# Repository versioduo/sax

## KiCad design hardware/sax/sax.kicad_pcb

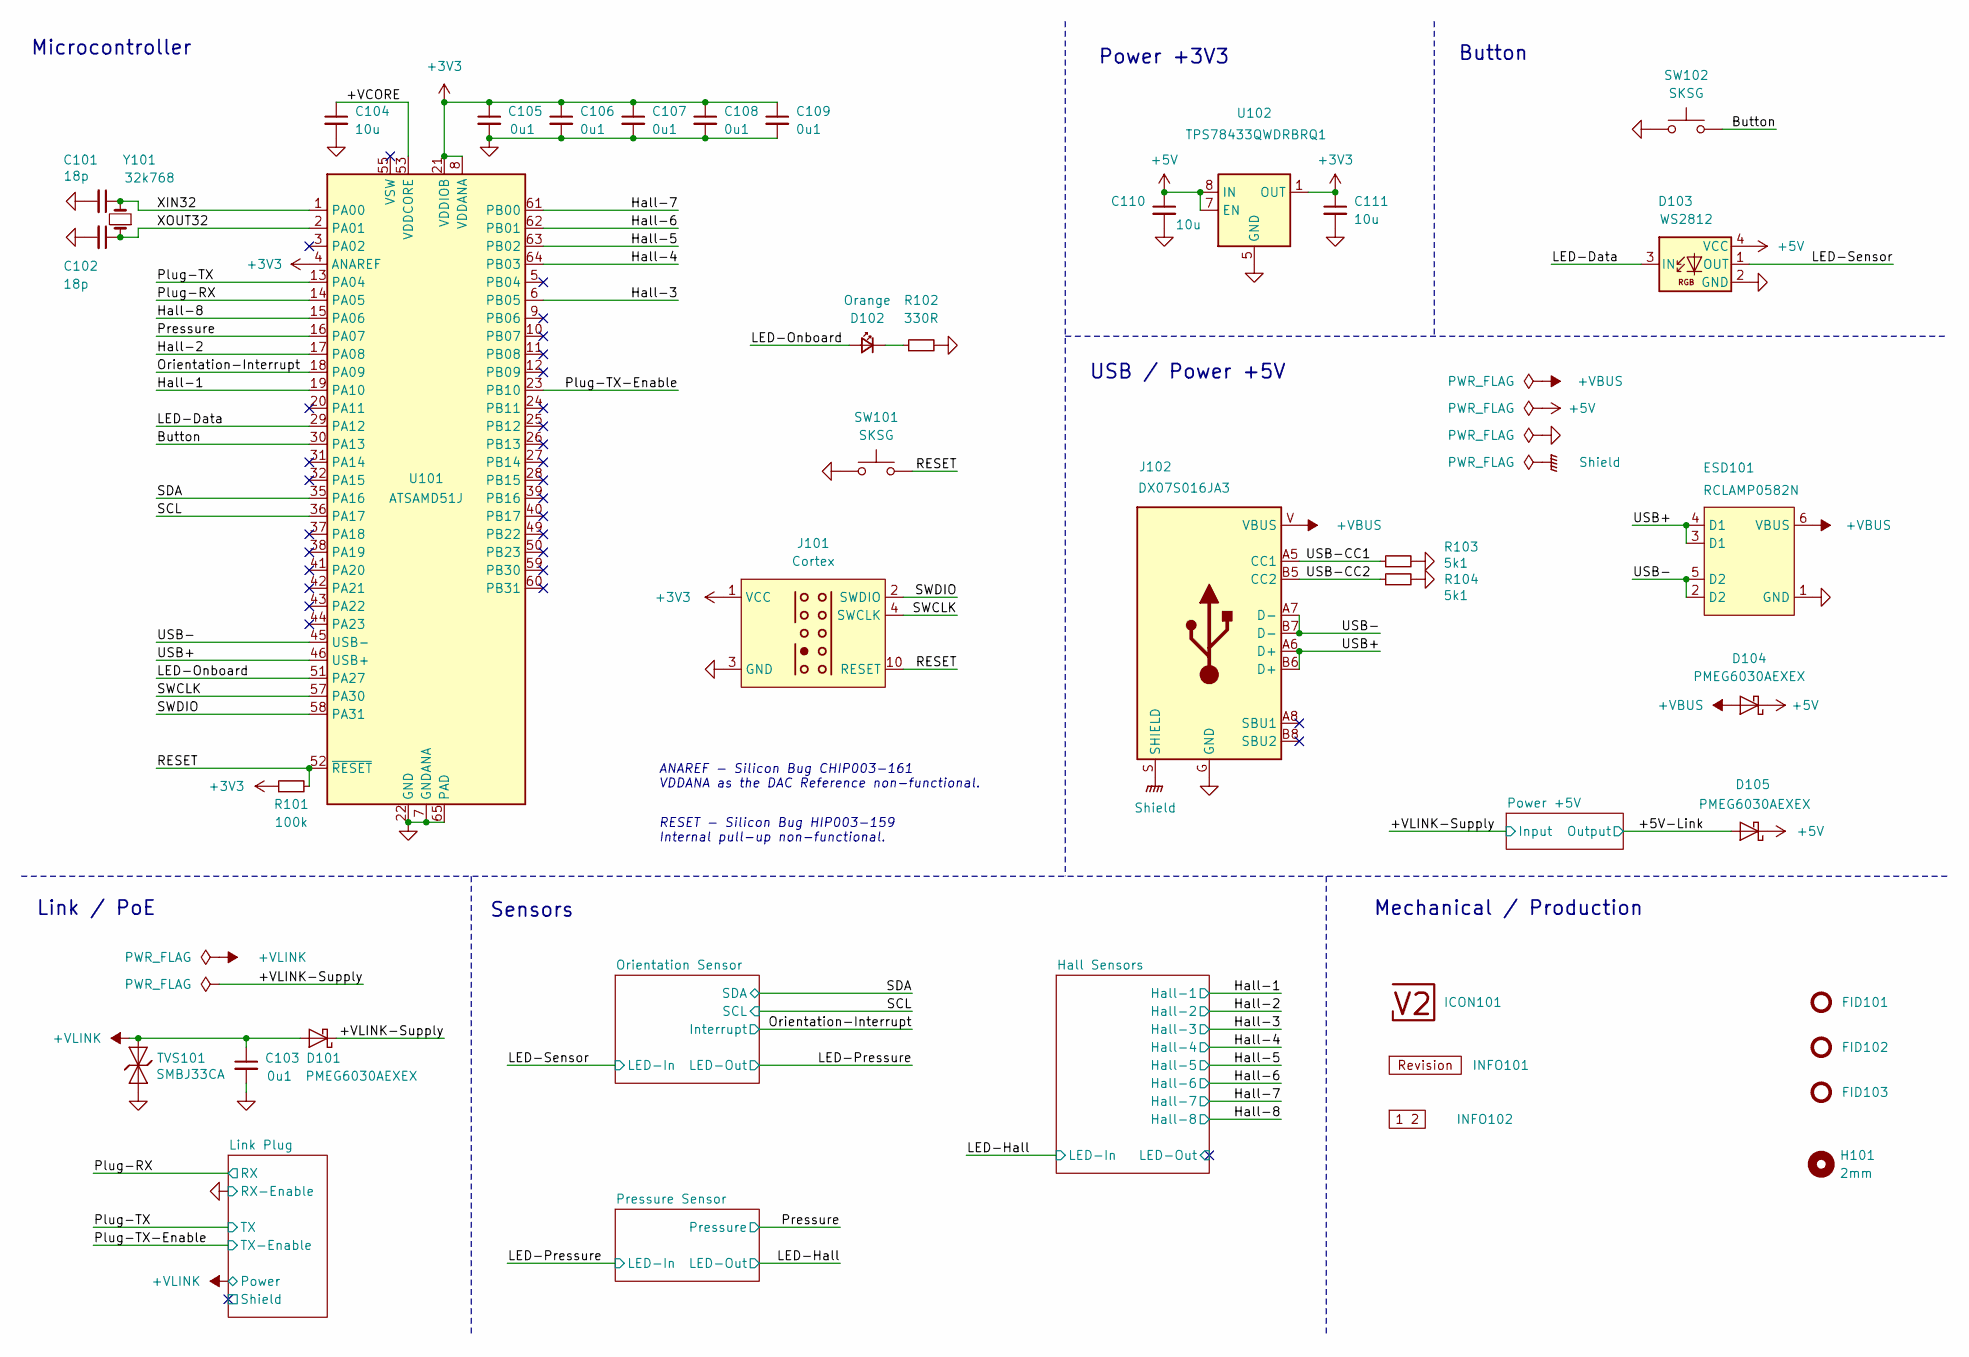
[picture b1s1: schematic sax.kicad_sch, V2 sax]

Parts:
C101, C102: 18p; C_1608; Rating 50V; Mouser 810-CGA3E2C0G1H180J
C103, C105, C106, C107, C108, C109: 0u1; C_1608; Rating 50V; Mouser 810-CGA3E2X7R1H104MA
C104: 10u; C_1608; Rating 10V; Mouser 810-C1608X6S1A106M
C110, C111: 10u; C_2012; Rating 25V; Mouser 810-C2012X5R1E106K
D101, D104, D105: PMEG6030AEXEX; D_SOD-123HP; Rating 60V; Mouser 771-PMEG6030AEXEX
D102: Orange; LED_1608; Rating 605nm; Mouser 755-SML-D12D1WT86
D103: WS2812; WS2812-2020; Rating 15mA; LCSC C965555
ESD101: RCLAMP0582N; SLP1210N6; Rating 20kV; Mouser 947-RCLAMP0582N.TCT
FID101, FID102, FID103: Fiducial_Paste; Fiducial_0.5mm_Mask1mm_Paste
H101: 2mm; MountingHole_2mm
ICON101: V2-logo; Logo_Small
INFO101: Revision
INFO102: Layer_Numbers-4
J101: Cortex
J102: DX07S016JA3; JAE_DX07S016JA3; Rating USB2.0; Mouser 656-DX07S016JA3R1500
R101: 100k; R_1608; Rating 100mW; Mouser 71-CRCW0603100KFKEAC
R102: 330R; R_1608; Rating 100mW; Mouser 71-CRCW0603330RFKEAC
R103, R104: 5k1; R_1608; Rating 100mW; Mouser 71-CRCW06035K10FKEAC
SW101, SW102: SKSG; Rating 1.6N; Mouser 688-SKSGACE010
TVS101: SMBJ33CA; D_SMB; Rating 33V; Mouser 652-SMBJ33CA-Q
U101: ATSAMD51J; QFN-64-1EP_9x9mm_P0.5mm_EP4.8x4.8mm_ThermalVias; Rating Cortex-M4F; Mouser 556-ATSAMD51J19AMU
U102: TPS78433QWDRBRQ1; VSON-8-1_3x3mm_P0.65_EP1.65x2.4mm; Rating 300mA; Mouser 595-TPS78433QWDRBRQ1
Y101: 32k768; Crystal_SMD_3215-2Pin_3.2x1.5mm; Rating 10ppm; Mouser 815-ABS0716632.768KT

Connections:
+3V3: C105.1, C106.1, C107.1, C108.1, C109.1, C111.1, J101.1 (VCC), R101.1, U101.4 (ANAREF), U101.8 (VDDANA), U101.21 (VDDIOB), U101.34 (VDDIO), U101.48 (VDDIO), U101.56 (VDDIO), U102.1 (OUT); also elsewhere on the board
+5V: C110.1, D103.4 (VCC), D104.1 (K), D105.1 (K), U102.7 (EN), U102.8 (IN); also elsewhere on the board
/+5V-Link: D105.2 (A); also elsewhere on the board
/+VBUS: D104.2 (A), ESD101.6 (VBUS), J102.V (VBUS)
/+VCORE: C104.1, U101.53 (VDDCORE)
/+VLINK: C103.1, D101.2 (A), TVS101.2 (A); also elsewhere on the board
/+VLINK-Supply: D101.1 (K); also elsewhere on the board
/Button: SW102.2, U101.30 (PA13)
/Hall-1: U101.19 (PA10); also elsewhere on the board
/Hall-2: U101.17 (PA08); also elsewhere on the board
/Hall-3: U101.6 (PB05); also elsewhere on the board
/Hall-4: U101.64 (PB03); also elsewhere on the board
/Hall-5: U101.63 (PB02); also elsewhere on the board
/Hall-6: U101.62 (PB01); also elsewhere on the board
/Hall-7: U101.61 (PB00); also elsewhere on the board
/Hall-8: U101.15 (PA06); also elsewhere on the board
/LED-Data: D103.3 (IN), U101.29 (PA12)
/LED-Onboard: D102.2 (A), U101.51 (PA27)
/LED-Sensor: D103.1 (OUT); also elsewhere on the board
/Orientation-Interrupt: U101.18 (PA09); also elsewhere on the board
/Plug-RX: U101.14 (PA05); also elsewhere on the board
/Plug-TX: U101.13 (PA04); also elsewhere on the board
/Plug-TX-Enable: U101.23 (PB10); also elsewhere on the board
/Pressure: U101.16 (PA07); also elsewhere on the board
/RESET: J101.10 (RESET), R101.2, SW101.2, U101.52 (~RESET)
/SCL: U101.36 (PA17); also elsewhere on the board
/SDA: U101.35 (PA16); also elsewhere on the board
/SWCLK: J101.4 (SWCLK), U101.57 (PA30)
/SWDIO: J101.2 (SWDIO), U101.58 (PA31)
/Shield: J102.S (SHIELD)
/USB+: ESD101.3 (D1), ESD101.4 (D1), J102.A6 (D+), J102.B6 (D+), U101.46 (USB+)
/USB-: ESD101.2 (D2), ESD101.5 (D2), J102.A7 (D-), J102.B7 (D-), U101.45 (USB-)
/USB-CC1: J102.A5 (CC1), R103.1
/USB-CC2: J102.B5 (CC2), R104.1
/XIN32: C101.1, U101.1 (PA00), Y101.2
/XOUT32: C102.1, U101.2 (PA01), Y101.1
GND: C101.2, C102.2, C103.2, C104.2, C105.2, C106.2, C107.2, C108.2, C109.2, C110.2, C111.2, D103.2 (GND), ESD101.1 (GND), J101.3 (GND), J101.5 (GND), J102.G (GND), R102.2, R103.2, R104.2, SW101.1, SW102.1, TVS101.1 (K), U101.7 (GNDANA), U101.22 (GND), U101.33 (GND), U101.47 (GND), U101.54 (GND), U101.65 (PAD), U102.5 (GND), U102.9 (GND); also elsewhere on the board
unnamed: D102.1 (K), R102.1

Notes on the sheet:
ANAREF - Silicon Bug CHIP003-161 VDDANA as the DAC Reference non-functional.
Sensors
Link / PoE
RESET - Silicon Bug HIP003-159 Internal pull-up non-functional.
Button
Power +3V3
Mechanical / Production
Microcontroller
USB / Power +5V

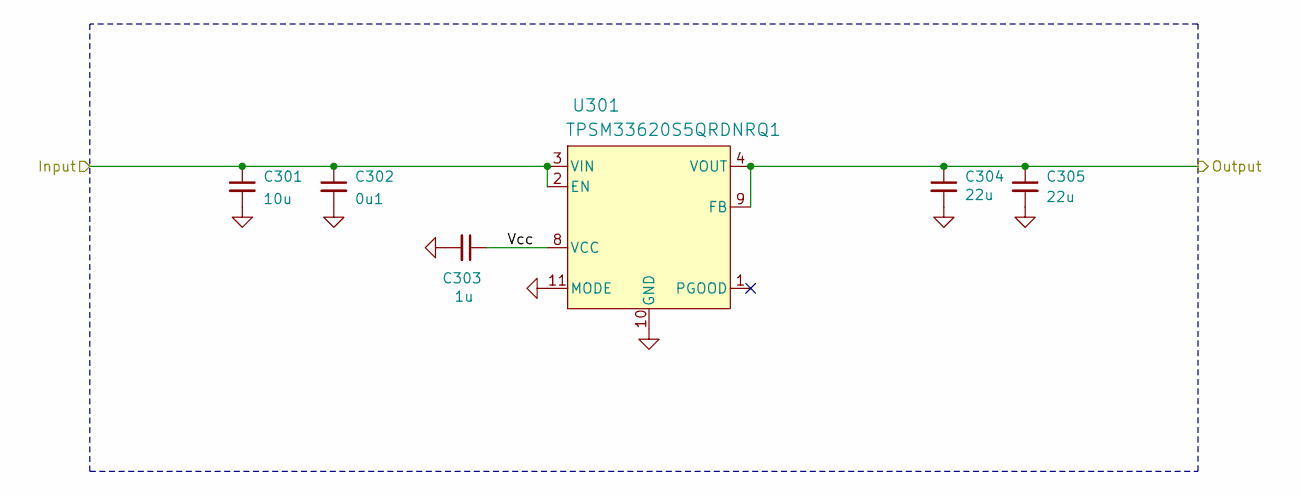
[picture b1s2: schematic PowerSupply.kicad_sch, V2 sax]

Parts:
C301: 10u; C_3225; Rating 50V; Mouser 810-CNC6P1X7R1H106K2
C302: 0u1; C_1608; Rating 50V; Mouser 810-CGA3E2X7R1H104MA
C303: 1u; C_1608; Rating 50V; Mouser 810-CGA3E3X7R1H105K0
C304, C305: 22u; C_3225; Rating 25V; Mouser 810-CGA6P3X7R1E226M5
U301: TPSM33620S5QRDNRQ1; QFN-11; Rating 2A; Mouser 595-SM33620S5QRDNRQ1

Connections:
/+5V-Link: C304.1, C305.1, U301.4 (VOUT), U301.9 (FB); also elsewhere on the board
/+VLINK-Supply: C301.1, C302.1, U301.2 (EN), U301.3 (VIN); also elsewhere on the board
/Power +5V/Vcc: C303.1, U301.8 (VCC)
GND: C301.2, C302.2, C303.2, C304.2, C305.2, U301.10 (GND), U301.11 (MODE); also elsewhere on the board

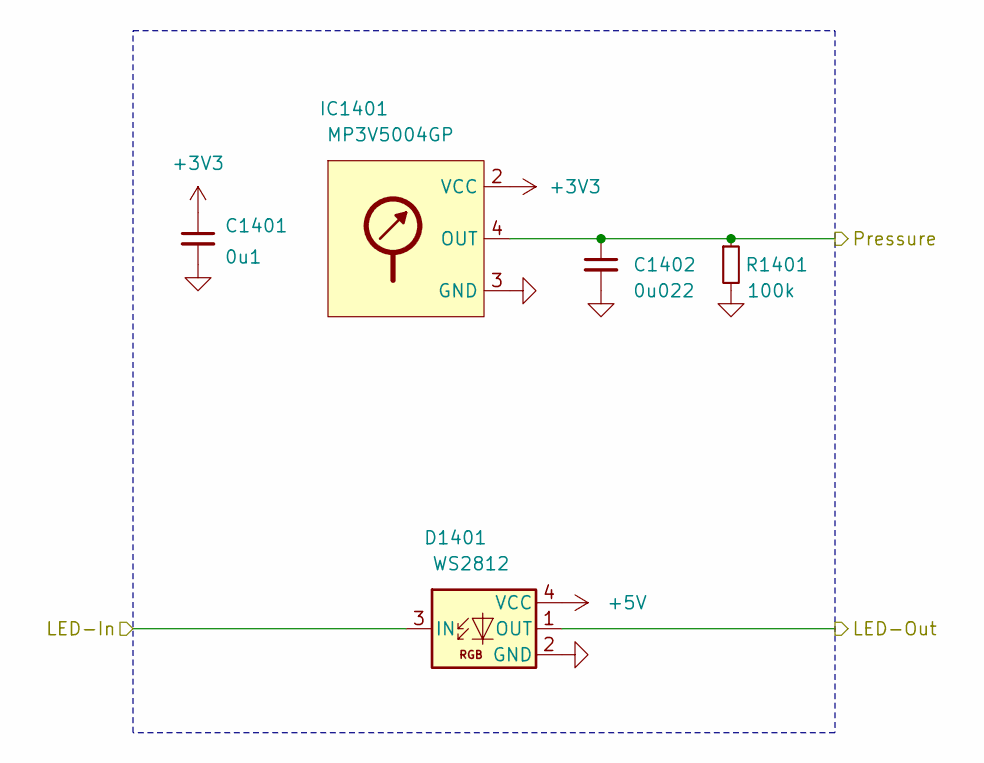
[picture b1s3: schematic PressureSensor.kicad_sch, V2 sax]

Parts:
C1401: 0u1; C_1608; Rating 50V; Mouser 810-CGA3E2X7R1H104MA
C1402: 0u022; C_1608; Rating 50V; Mouser 603-CC603KPX7R9BB223
D1401: WS2812; WS2812-2020; Rating 15mA; LCSC C965555
IC1401: MP3V5004GP; Rating 3.92 kPa; Mouser 841-MP3V5004GP
R1401: 100k; R_1608; Rating 100mW; Mouser 71-CRCW0603100KFKEAC

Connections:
+3V3: C1401.1, IC1401.2 (VCC); also elsewhere on the board
+5V: D1401.4 (VCC); also elsewhere on the board
/LED-Hall: D1401.1 (OUT); also elsewhere on the board
/LED-Pressure: D1401.3 (IN); also elsewhere on the board
/Pressure: C1402.1, IC1401.4 (OUT), R1401.1; also elsewhere on the board
GND: C1401.2, C1402.2, D1401.2 (GND), IC1401.3 (GND), R1401.2; also elsewhere on the board

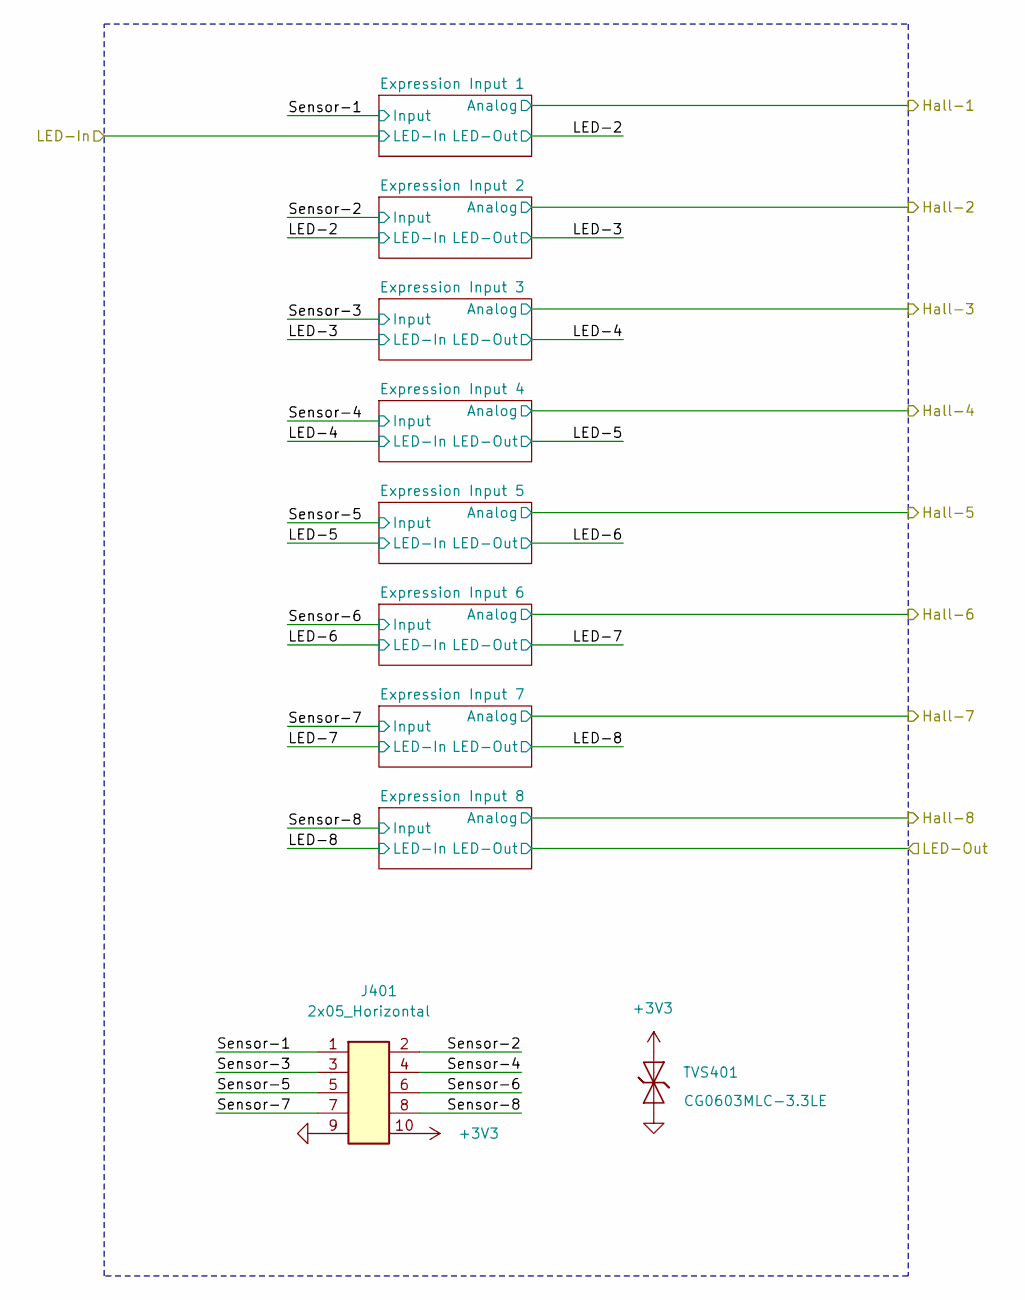
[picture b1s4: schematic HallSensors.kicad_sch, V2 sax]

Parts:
J401: 2x05_Horizontal; PinHeader_2x05_P1.27mm_Horizontal; Rating 1A; Mouser 649-200211120001T4LF
TVS401: CG0603MLC-3.3LE; D_1608; Rating 3V3; Mouser 652-CG0603MLC-3.3LE

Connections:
+3V3: J401.10, TVS401.1 (K); also elsewhere on the board
/Hall Sensors/Sensor-1: J401.1; also elsewhere on the board
/Hall Sensors/Sensor-2: J401.2; also elsewhere on the board
/Hall Sensors/Sensor-3: J401.3; also elsewhere on the board
/Hall Sensors/Sensor-4: J401.4; also elsewhere on the board
/Hall Sensors/Sensor-5: J401.5; also elsewhere on the board
/Hall Sensors/Sensor-6: J401.6; also elsewhere on the board
/Hall Sensors/Sensor-7: J401.7; also elsewhere on the board
/Hall Sensors/Sensor-8: J401.8; also elsewhere on the board
GND: J401.9, TVS401.2 (A); also elsewhere on the board

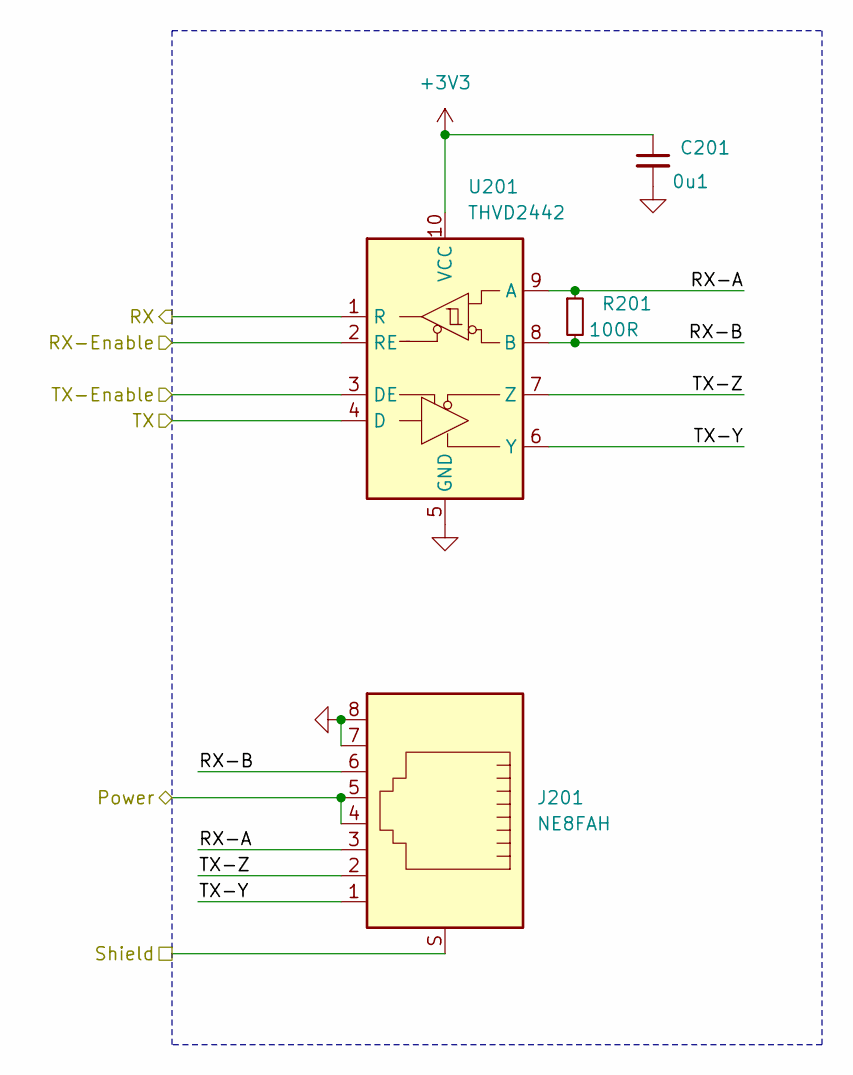
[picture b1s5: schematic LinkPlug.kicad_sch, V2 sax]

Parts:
C201: 0u1; C_1608; Rating 50V; Mouser 810-CGA3E2X7R1H104MA
J201: NE8FAH; Rating CAT5e; Mouser 568-NE8FAH
R201: 100R; R_1608; Rating 330mW; Mouser 71-CRCW0603100RFKEAH
U201: THVD2442; VSON-10-4-1EP_3x3mm_P0.5mm_EP1.65x2.4mm_ThermalVias; Rating 20Mbps; Mouser 595-THVD2442DRCR

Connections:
+3V3: C201.1, U201.10 (VCC); also elsewhere on the board
/+VLINK: J201.4, J201.5; also elsewhere on the board
/Link Plug/RX-A: J201.3, R201.1, U201.9 (A)
/Link Plug/RX-B: J201.6, R201.2, U201.8 (B)
/Link Plug/Shield: J201.S
/Link Plug/TX-Y: J201.1, U201.6 (Y)
/Link Plug/TX-Z: J201.2, U201.7 (Z)
/Plug-RX: U201.1 (R); also elsewhere on the board
/Plug-TX: U201.4 (D); also elsewhere on the board
/Plug-TX-Enable: U201.3 (DE); also elsewhere on the board
GND: C201.2, J201.7, J201.8, U201.2 (RE), U201.5 (GND), U201.11 (GND); also elsewhere on the board

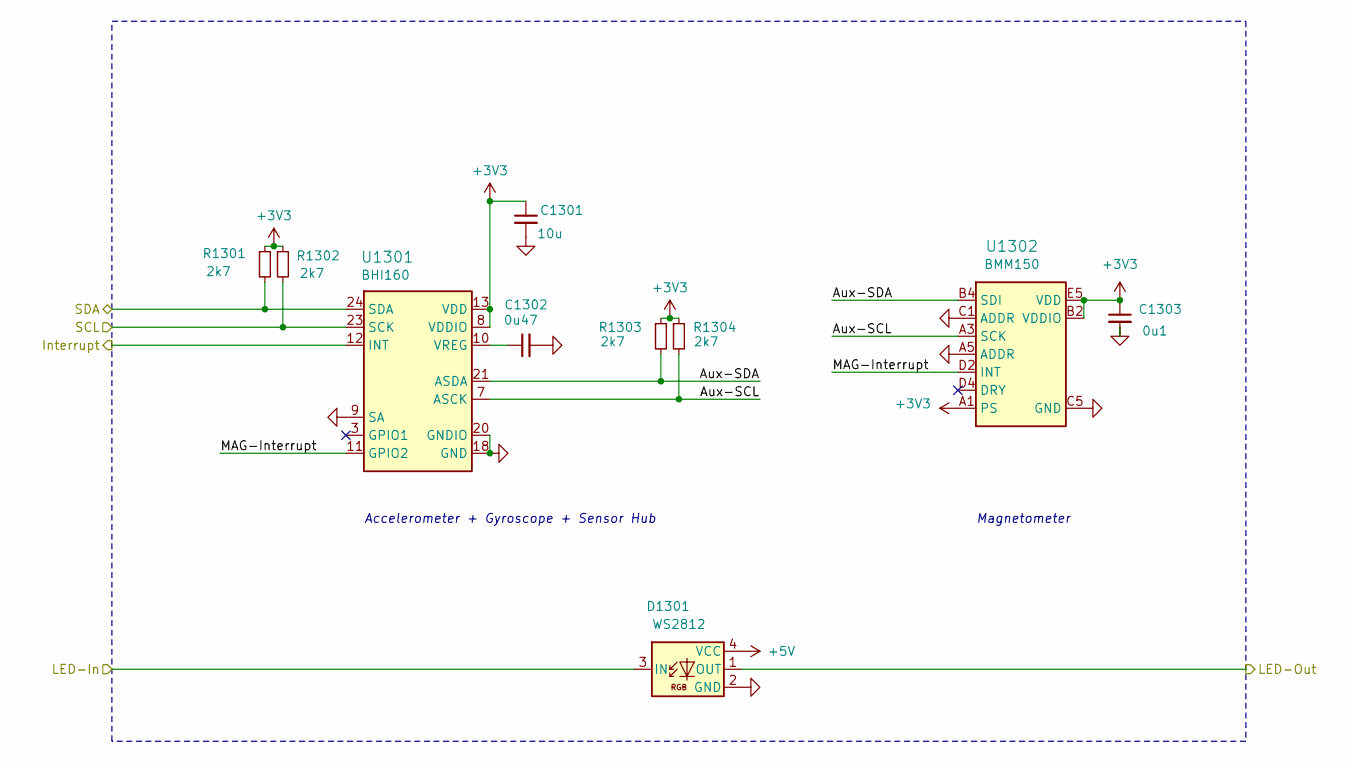
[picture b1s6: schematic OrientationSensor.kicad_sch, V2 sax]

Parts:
C1301: 10u; C_1608; Rating 10V; Mouser 810-C1608X6S1A106M
C1302: 0u47; C_1608; Rating 50V; Mouser 810-CGA3E3X7R1H474KB
C1303: 0u1; C_1608; Rating 50V; Mouser 810-CGA3E2X7R1H104MA
D1301: WS2812; WS2812-2020; Rating 15mA; LCSC C965555
R1301, R1302, R1303, R1304: 2k7; R_1608; Rating 100mW; Mouser 71-CRCW06032K70FKEAC
U1301: BHI160; LGA24-3x3; LCSC C464452
U1302: BMM150; WLCSP-1.56x1.56; LCSC C171681

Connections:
+3V3: C1301.1, C1303.1, R1301.1, R1302.1, R1303.1, R1304.1, U1301.8 (VDDIO), U1301.13 (VDD), U1302.A1 (PS), U1302.B2 (VDDIO), U1302.E5 (VDD); also elsewhere on the board
+5V: D1301.4 (VCC); also elsewhere on the board
/LED-Pressure: D1301.1 (OUT); also elsewhere on the board
/LED-Sensor: D1301.3 (IN); also elsewhere on the board
/Orientation Sensor/Aux-SCL: R1304.2, U1301.7 (ASCK), U1302.A3 (SCK)
/Orientation Sensor/Aux-SDA: R1303.2, U1301.21 (ASDA), U1302.B4 (SDI)
/Orientation Sensor/MAG-Interrupt: U1301.11 (GPIO2), U1302.D2 (INT)
/Orientation-Interrupt: U1301.12 (INT); also elsewhere on the board
/SCL: R1302.2, U1301.23 (SCK); also elsewhere on the board
/SDA: R1301.2, U1301.24 (SDA); also elsewhere on the board
GND: C1301.2, C1302.2, C1303.2, D1301.2 (GND), U1301.9 (SA), U1301.18 (GND), U1301.20 (GNDIO), U1302.A5 (ADDR), U1302.C1 (ADDR), U1302.C5 (GND), U1302.E1 (GND), U1302.E3 (GND); also elsewhere on the board
unnamed: C1302.1, U1301.10 (VREG)

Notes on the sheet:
Accelerometer + Gyroscope + Sensor Hub
Magnetometer

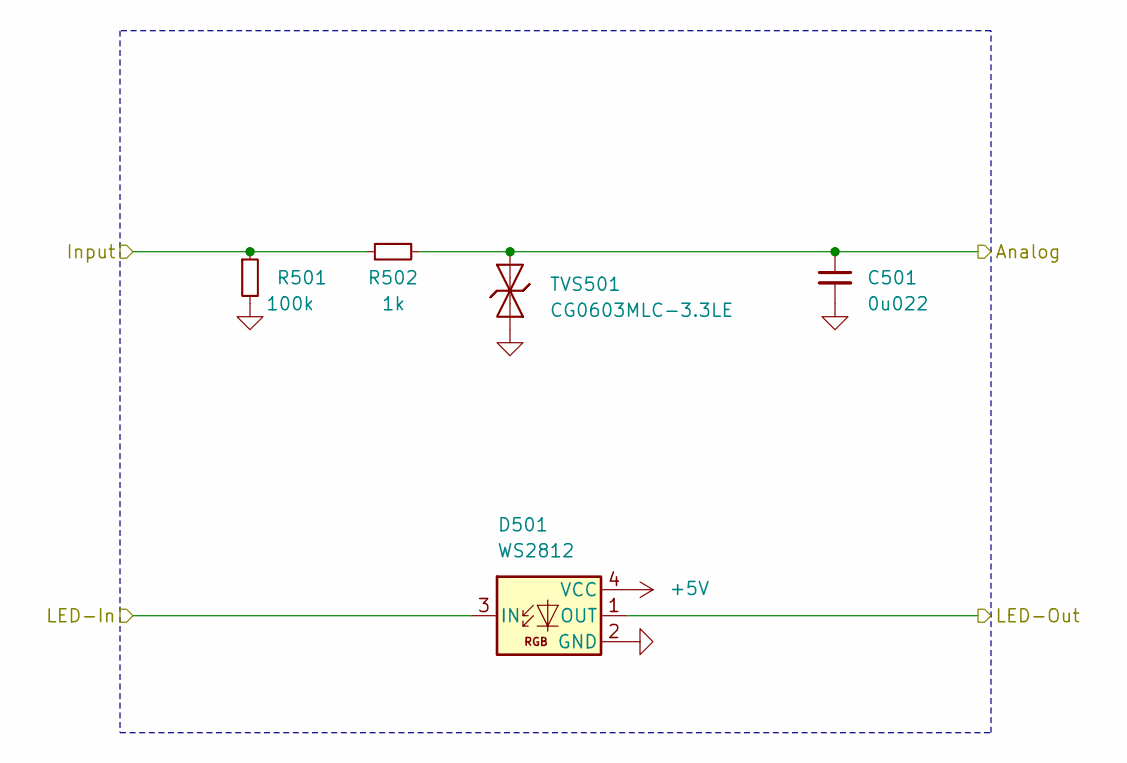
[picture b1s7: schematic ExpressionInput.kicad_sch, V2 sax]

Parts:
C501: 0u022; C_1608; Rating 50V; Mouser 603-CC603KPX7R9BB223
D501: WS2812; WS2812-2020; Rating 15mA; LCSC C965555
R501: 100k; R_1608; Rating 100mW; Mouser 71-CRCW0603100KFKEAC
R502: 1k; R_1608; Rating 330mW; Mouser 71-CRCW06031K00FKEAH
TVS501: CG0603MLC-3.3LE; D_1608; Rating 3V3; Mouser 652-CG0603MLC-3.3LE

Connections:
+5V: D501.4 (VCC); also elsewhere on the board
/Hall Sensors/LED-2: D501.1 (OUT); also elsewhere on the board
/Hall Sensors/Sensor-1: R501.1, R502.2; also elsewhere on the board
/Hall-1: C501.1, R502.1, TVS501.2 (A); also elsewhere on the board
/LED-Hall: D501.3 (IN); also elsewhere on the board
GND: C501.2, D501.2 (GND), R501.2, TVS501.1 (K); also elsewhere on the board

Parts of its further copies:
C601, C701, C801, C901, C1001, C1101, C1201: 0u022; C_1608; Rating 50V; Mouser 603-CC603KPX7R9BB223
D601, D701, D801, D901, D1001, D1101, D1201: WS2812; WS2812-2020; Rating 15mA; LCSC C965555
R601, R701, R801, R901, R1001, R1101, R1201: 100k; R_1608; Rating 100mW; Mouser 71-CRCW0603100KFKEAC
R602, R702, R802, R902, R1002, R1102, R1202: 1k; R_1608; Rating 330mW; Mouser 71-CRCW06031K00FKEAH
TVS601, TVS701, TVS801, TVS901, TVS1001, TVS1101, TVS1201: CG0603MLC-3.3LE; D_1608; Rating 3V3; Mouser 652-CG0603MLC-3.3LE

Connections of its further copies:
+5V: D601.4 (VCC), D701.4 (VCC), D801.4 (VCC), D901.4 (VCC), D1001.4 (VCC), D1101.4 (VCC), D1201.4 (VCC); also elsewhere on the board
/Hall Sensors/LED-2: D601.3 (IN); also elsewhere on the board
/Hall Sensors/LED-3: D601.1 (OUT), D701.3 (IN)
/Hall Sensors/LED-4: D701.1 (OUT), D801.3 (IN)
/Hall Sensors/LED-5: D801.1 (OUT), D901.3 (IN)
/Hall Sensors/LED-6: D901.1 (OUT), D1001.3 (IN)
/Hall Sensors/LED-7: D1001.1 (OUT), D1101.3 (IN)
/Hall Sensors/LED-8: D1101.1 (OUT), D1201.3 (IN)
/Hall Sensors/LED-Out: D1201.1 (OUT)
/Hall Sensors/Sensor-2: R601.1, R602.2; also elsewhere on the board
/Hall Sensors/Sensor-3: R701.1, R702.2; also elsewhere on the board
/Hall Sensors/Sensor-4: R801.1, R802.2; also elsewhere on the board
/Hall Sensors/Sensor-5: R901.1, R902.2; also elsewhere on the board
/Hall Sensors/Sensor-6: R1001.1, R1002.2; also elsewhere on the board
/Hall Sensors/Sensor-7: R1101.1, R1102.2; also elsewhere on the board
/Hall Sensors/Sensor-8: R1201.1, R1202.2; also elsewhere on the board
/Hall-2: C601.1, R602.1, TVS601.2 (A); also elsewhere on the board
/Hall-3: C701.1, R702.1, TVS701.2 (A); also elsewhere on the board
/Hall-4: C801.1, R802.1, TVS801.2 (A); also elsewhere on the board
/Hall-5: C901.1, R902.1, TVS901.2 (A); also elsewhere on the board
/Hall-6: C1001.1, R1002.1, TVS1001.2 (A); also elsewhere on the board
/Hall-7: C1101.1, R1102.1, TVS1101.2 (A); also elsewhere on the board
/Hall-8: C1201.1, R1202.1, TVS1201.2 (A); also elsewhere on the board
GND: C601.2, C701.2, C801.2, C901.2, C1001.2, C1101.2, C1201.2, D601.2 (GND), D701.2 (GND), D801.2 (GND), D901.2 (GND), D1001.2 (GND), D1101.2 (GND), D1201.2 (GND), R601.2, R701.2, R801.2, R901.2, R1001.2, R1101.2, R1201.2, TVS601.1 (K), TVS701.1 (K), TVS801.1 (K), TVS901.1 (K), TVS1001.1 (K), TVS1101.1 (K), TVS1201.1 (K); also elsewhere on the board

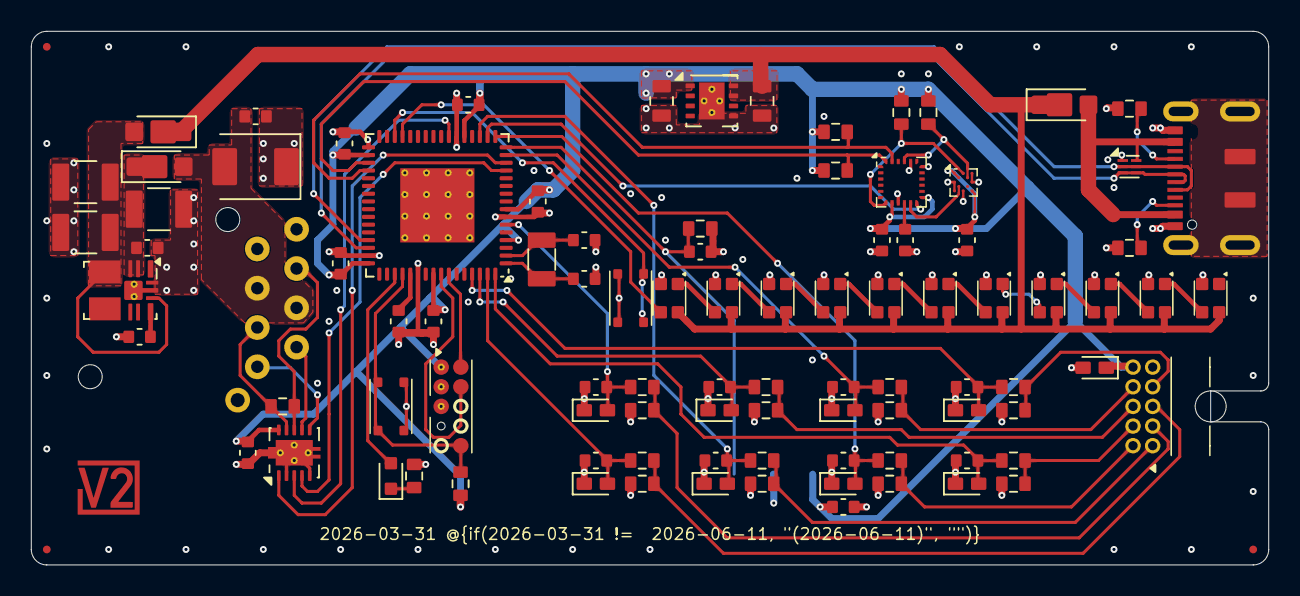
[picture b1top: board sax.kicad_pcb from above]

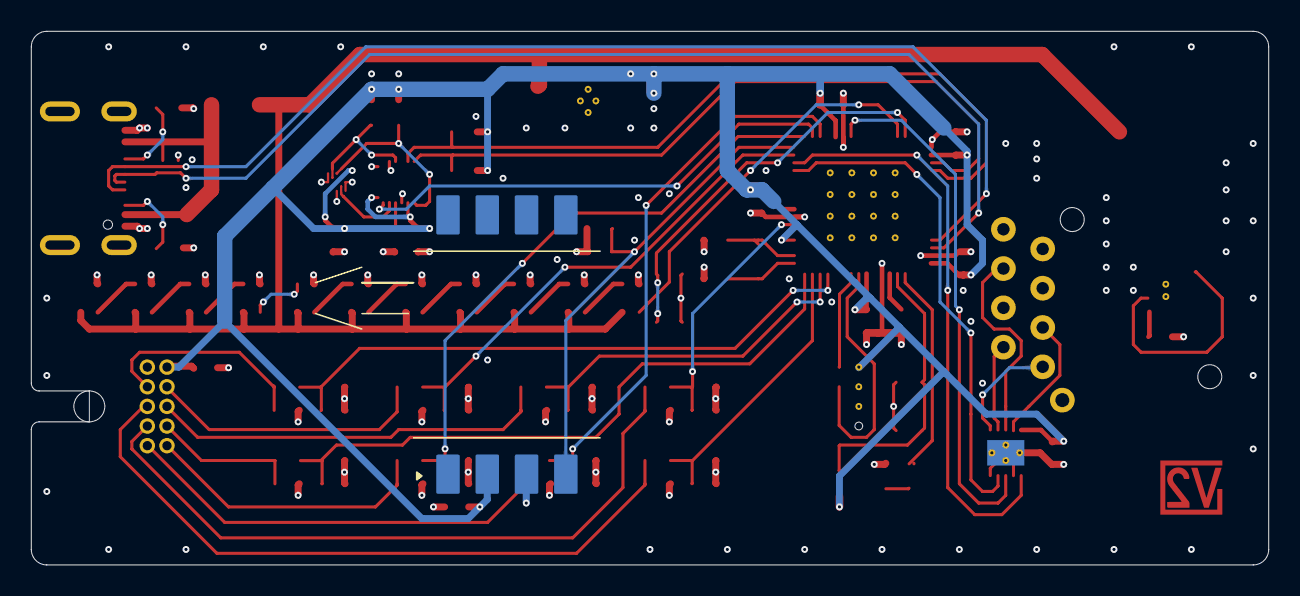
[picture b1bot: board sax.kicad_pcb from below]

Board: 4 copper layers, 80.0 x 34.5 mm, 103 parts (2 on the bottom side), 63 nets.

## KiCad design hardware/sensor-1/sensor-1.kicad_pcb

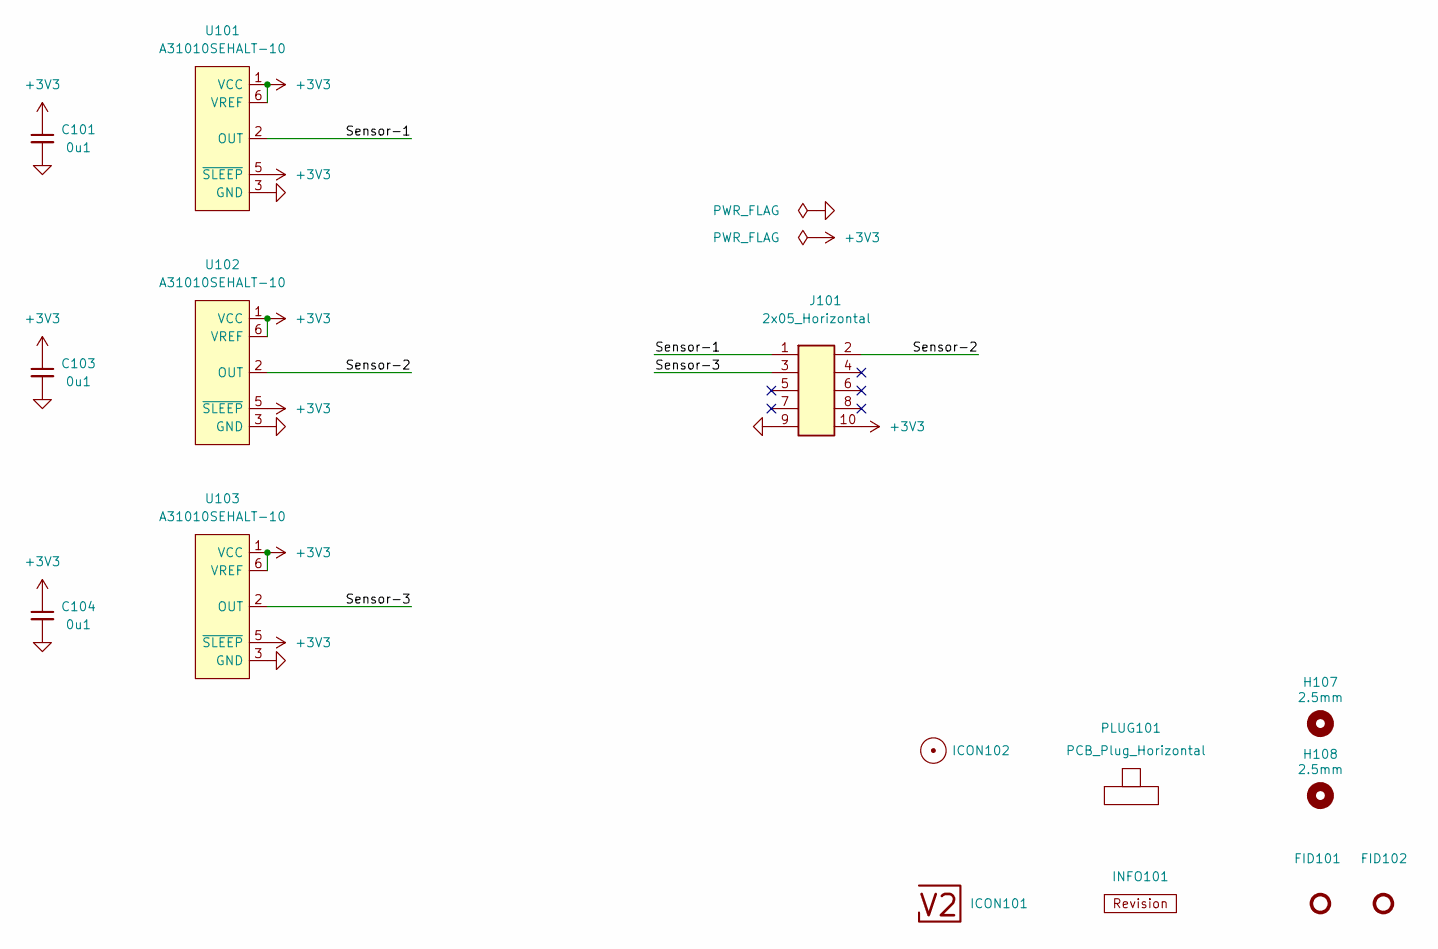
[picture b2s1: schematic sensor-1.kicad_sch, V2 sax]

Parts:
C101, C103, C104: 0u1; C_0603; Rating 50V; Mouser 810-CGA3E2X7R1H104MA
FID101, FID102: Fiducial_Paste; Fiducial_0.5mm_Mask1mm_Paste
H107, H108: 2.5mm; MountingHole_2.5mm
ICON101: V2-logo; Logo_Small
ICON102: Dot; Dot_Small
INFO101: Revision
J101: 2x05_Horizontal; PinHeader_2x05_P1.27mm_Horizontal; Rating 1A; Mouser 649-200211120001T4LF
PLUG101: PCB_Plug_Horizontal
U101, U102, U103: A31010SEHALT-10; A31010SEHALT10; Rating 10mV/G; Mouser 250-A31010SEHALT-10

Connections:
+3V3: C101.1, C103.1, C104.1, J101.10, U101.1 (VCC), U101.5 (~SLEEP), U101.6 (VREF), U102.1 (VCC), U102.5 (~SLEEP), U102.6 (VREF), U103.1 (VCC), U103.5 (~SLEEP), U103.6 (VREF)
/Sensor-1: J101.1, U101.2 (OUT)
/Sensor-2: J101.2, U102.2 (OUT)
/Sensor-3: J101.3, U103.2 (OUT)
GND: C101.2, C103.2, C104.2, J101.9, U101.3 (GND), U102.3 (GND), U103.3 (GND)

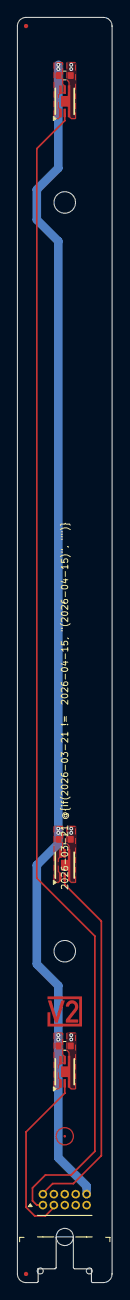
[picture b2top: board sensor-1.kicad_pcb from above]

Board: 2 copper layers, 11.0 x 147.0 mm, 15 parts (0 on the bottom side), 5 nets.

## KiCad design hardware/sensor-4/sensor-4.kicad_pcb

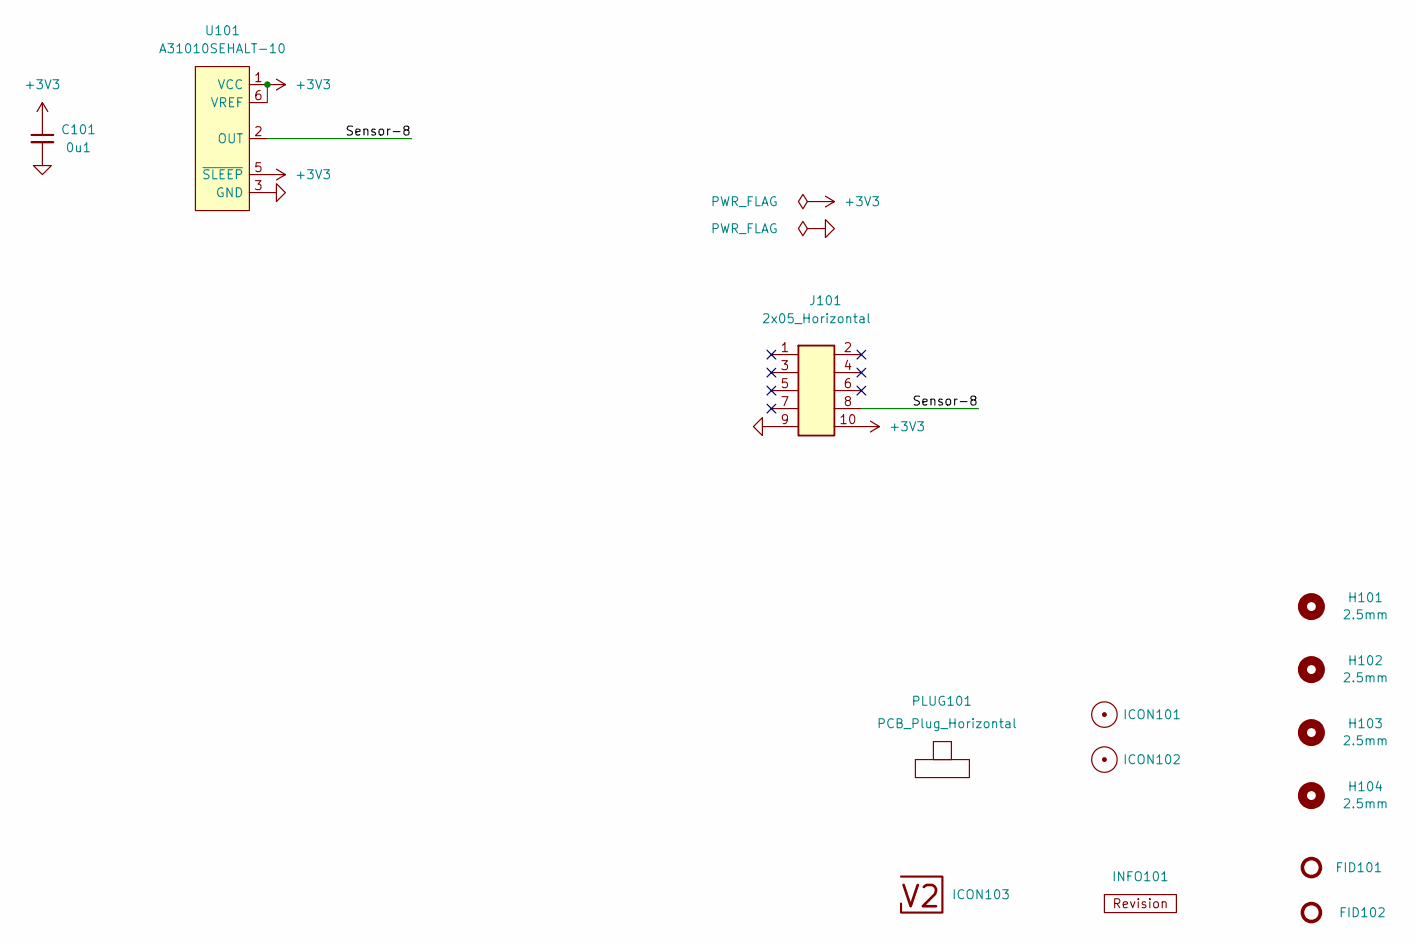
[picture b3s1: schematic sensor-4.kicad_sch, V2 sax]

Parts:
C101: 0u1; C_0603; Rating 50V; Mouser 810-CGA3E2X7R1H104MA
FID101, FID102: Fiducial_Paste; Fiducial_0.5mm_Mask1mm_Paste
H101, H102, H103, H104: 2.5mm; MountingHole_2.5mm
ICON101, ICON102: Dot; Dot_Small
ICON103: V2-logo; Logo_Small
INFO101: Revision
J101: 2x05_Horizontal; PinHeader_2x05_P1.27mm_Horizontal; Mouser 649-200211120001T4LF
PLUG101: PCB_Plug_Horizontal
U101: A31010SEHALT-10; A31010SEHALT10; Mouser 250-A31010SEHALT-10

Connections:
+3V3: C101.1, J101.10, U101.1 (VCC), U101.5 (~SLEEP), U101.6 (VREF)
/Sensor-8: J101.8, U101.2 (OUT)
GND: C101.2, J101.9, U101.3 (GND)

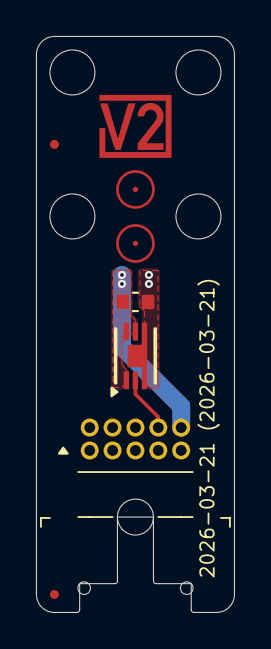
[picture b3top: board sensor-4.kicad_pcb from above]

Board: 2 copper layers, 11.0 x 32.0 mm, 14 parts (0 on the bottom side), 3 nets.
